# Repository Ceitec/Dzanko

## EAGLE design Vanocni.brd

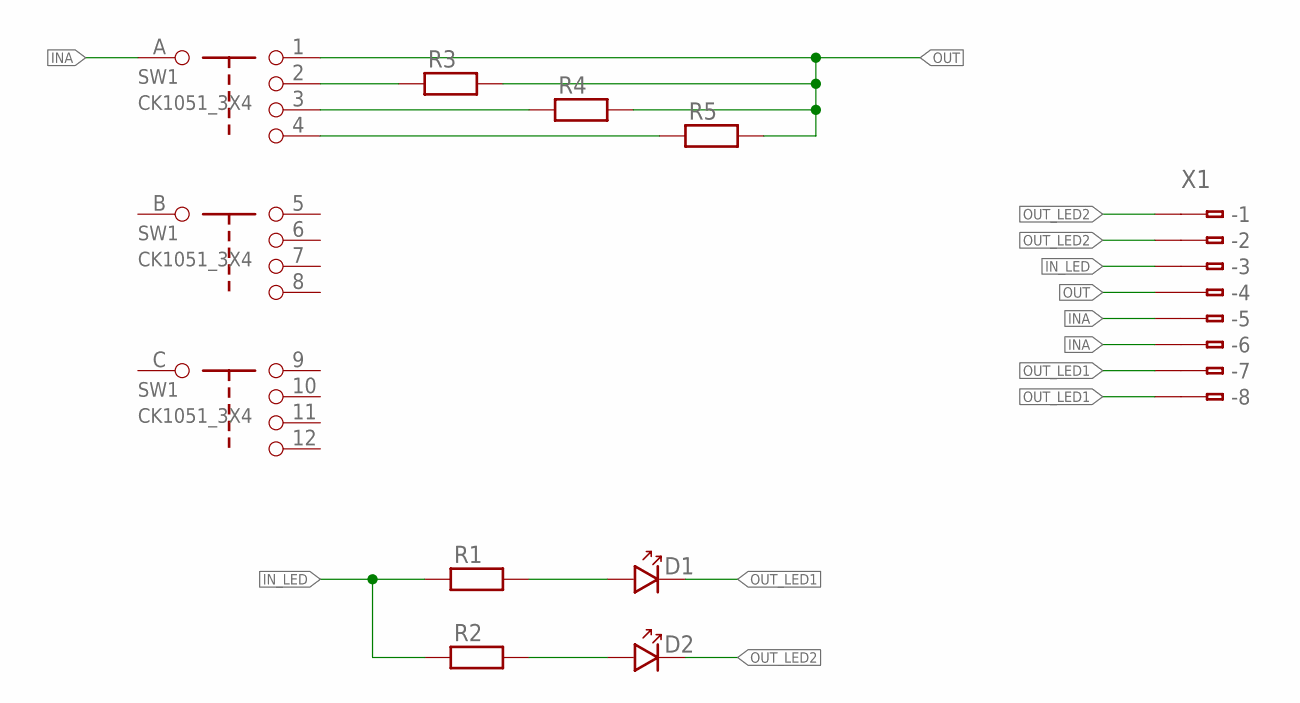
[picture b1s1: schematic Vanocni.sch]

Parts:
D1, D2: LED_5
R1, R2: R_7,5; R-7,5
R3, R4, R5: R__2W; R-_2W
SW1: CK1051_3X4; SWITCH3X4
X1: 233-508

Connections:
INA: SW1.A, X1.B5 (B-5), X1.B6 (B-6)
IN_LED: R1.1, R2.1, X1.B3 (B-3)
unnamed: D1.A, R1.2
unnamed: D2.A, R2.2
unnamed: R3.1, SW1.2
unnamed: R4.1, SW1.3
unnamed: R5.1, SW1.4
OUT: R3.2, R4.2, R5.2, SW1.1, X1.B4 (B-4)
OUT_LED1: D1.K, X1.B7 (B-7), X1.B8 (B-8)
OUT_LED2: D2.K, X1.B1 (B-1), X1.B2 (B-2)

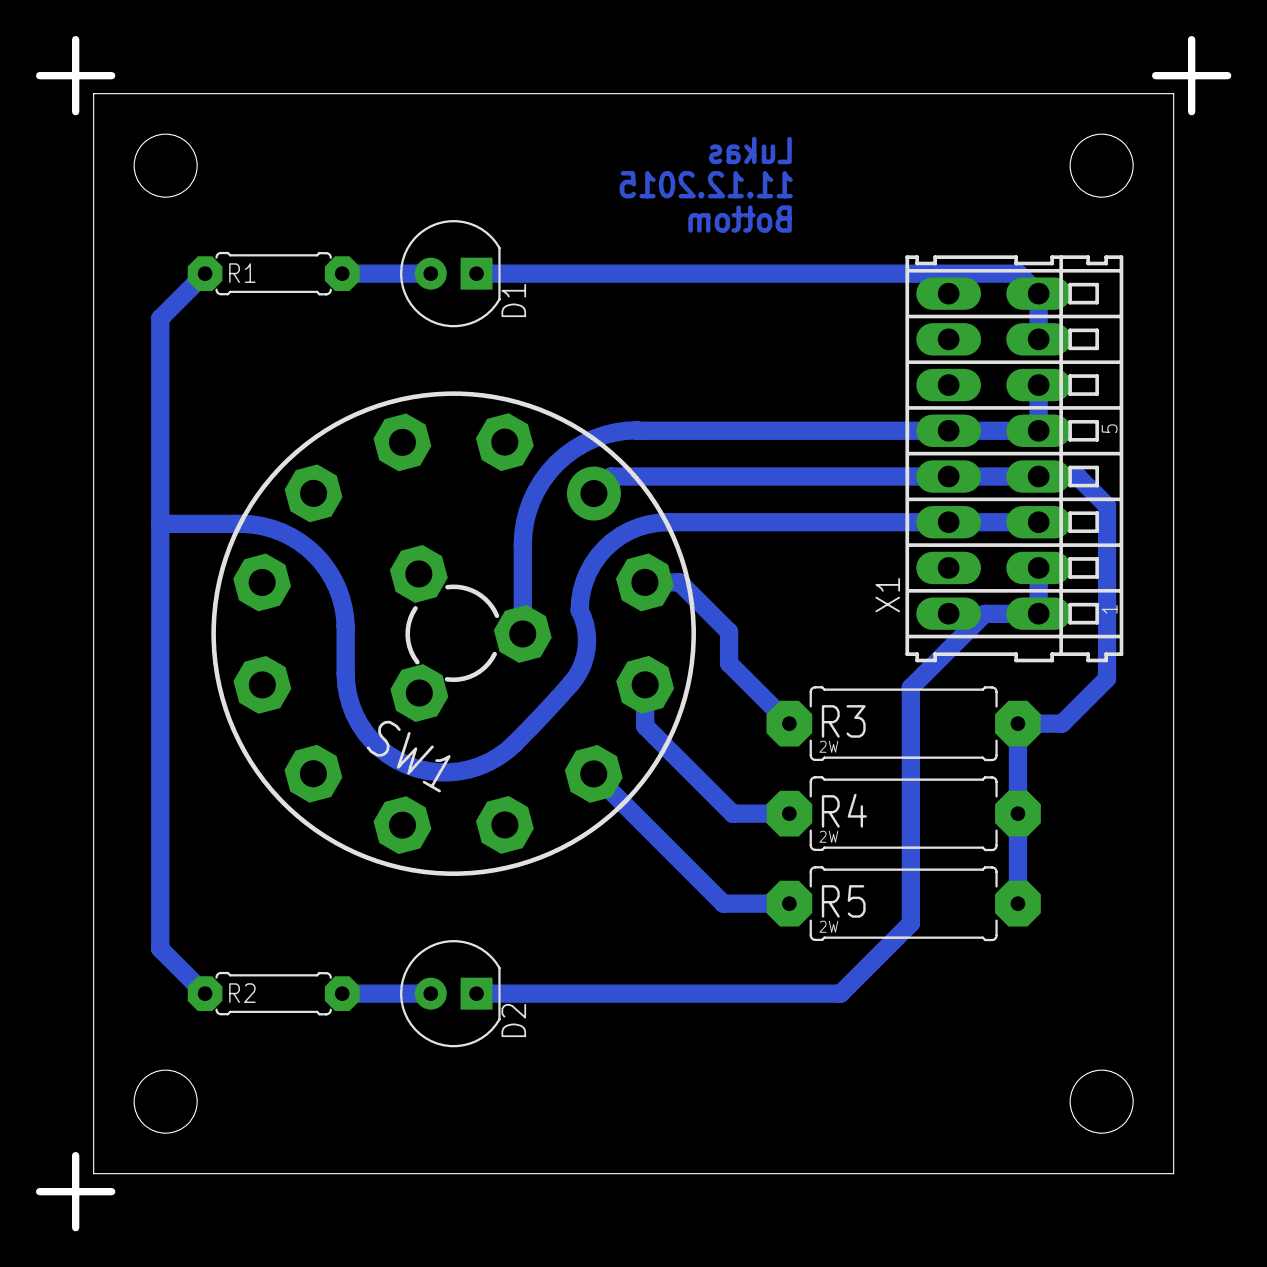
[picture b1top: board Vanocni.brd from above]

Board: 2 copper layers, 66.0 x 66.0 mm, 9 parts (0 on the bottom side), 10 nets.

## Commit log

2015-12-11 :circus_tent: Added .gitattributes & .gitignore files
2015-12-11 v.1.1.0.0

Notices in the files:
parts and their libraries:
Copyright (C) PaJa 2001-2014
Copyright (C) PaJa 2011-2014
